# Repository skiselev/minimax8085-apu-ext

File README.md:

# minimax8085-apu-ext
Arithmetic Processor and Extension Board for MiniMax 8085 SBC

## Introduction

The MiniMax 8085 Arithmetic Processor and Extension board adds to [MiniMax 8085 SBC](https://github.com/skiselev/minimax8085) an AMD Am9511A / Intel 8231A Arithmetic Processor Unit (APU), Intel 8255 Programmable Parallel Interface (PPI), Intel 8254 Programmable Interrupt Timer (PIT), and switchable 32 KiB SRAM, that can swapped in instead of MiniMax 8085 on-board ROM. 
It is designed to be plugged on the top of MiniMax8085 using 2x20 pin header / pin socket.

## Hardware Documentation

### Schematic and PCB Layout

[Schematic - Version 1.1](KiCad/Mini8085Ext-Schematic-1.1.pdf)

[PCB Layout - Version 1.1](KiCad/Mini8085Ext-Board-1.1.pdf)

### Design Description

#### Address Decode / Chip Select

The Arithmetic Processor and Extension board uses 74HCT138 3-to-8 decoder U5 for address decode:
* Enable signal E3 of 74HCT138 is connected to IO/M signal, and therefore the decoder is enabled only during I/O operations, when IO/M signal value is HIGH
* Enable signals /E1 and /E2 of 74HCT138 are connected to address lines A6 and A7, so that decoder is enabled when both of these signals are low - 0x00 - 0x3F address range
* Inputs A0-A2 of 74HCT138 are connected to address lines A3 - A4, therefore each output of 74HCT138 is active (LOW) for a block of 8 consequitive I/O addresses, /O0 - for 0x00-0x07, /O1 - for 0x08-0x0F, ... , /O6 for 0x30-0x37, and /O6 for 0x38-0x3F
* Output /O2 of 74HCT138 - /CFG_CS signal - is connected to the input of the 74HCT32 OR gate U8D, another input of that gate is connected to /WD signal. As the result, the output of the gate U8D - CFG_WR is active (LOW) during write cycles to 0x10-0x17 I/O range. CFG_WR is used as a clock signal for 74HCT74 flip-flop U7B, which output /Q is connected to /ROM_DIS signal, that disables MiniMax 8085 on-board ROM, and enables the SRAM on the extension board
* Output /O3 of 74HCT138 - /PPI_CS signal - is connected to the /CS input of 8255 PPI U2, therefore the PPI can be accessed using 0x18 - 0x1F address range
* Output /O4 of 74HCT138 - /PIT_CS signal - is connected to the /CS input of 8254 PIT U3, therefore the PIT can be accessed using 0x20 - 0x27 address range
* Output /O5 of 74HCT138 - /APU_CS signal - is connected to the /CS input of 8231 APU U1, therefore the APU can be accessed using 0x28 - 0x2F address range

#### Arithmetic Processor Unit

Intel 8131A/AMD Am9511A APU is accessed using I/O ports in range 0x28 - 0x2F. The APU uses the lower address bit A0 to select between data register (A0 = 0, I/O address - 0x28) or command/status register (A1 = 1, I/O address - 0x29). The APU is programmed by entering the data into its stack by writing the data register, and then sending the command by writting it to the command register. Once the command completes, the APU will issue an interrupt, which is connected to 8085 TRAP (unmaskable interrupt) signal. The results can be read then from the stack by reading the data register. Please refer to the [Intel 8231A APU Datasheet](Documentation/Intel-8231A_APU-Datasheet.pdf) and the [AMD Am9511A/Am9512 Floating Point Processor Manual](Documentation/AMD-Am9511A-9512-FP_Processor_Manual.pdf) for the detailed programming information.

The APU interface also includes a wait cycle generator built using two 74HCT74 flip flops U6A and U6B, and a few logic gates - U8C, U9A, U9B. This logic generates one or more states when APU is accessed, depending on the /PAUSE output of the APU. The READY signal - pin 1 on header J1 must be connected to the READY signal on MiniMax 8085. Note that READY signal is not provided on the extension connector, therefore a short wire should be used instead.

#### Programmable Parallel Interface

Intel 8255 PPI is accessed using I/O ports in range 0x18 - 0x1F. All the PPI I/O pins are routed to the connector J4. This connector also provides ground and fused 5V power supply. It can be used to connect PPIDE, Extension ROMs, or other peripherals.

Please refer to [Intel 8255 PPI Datasheet](Documentation/Intel-8255_PPI-Datasheet.pdf) for programming information

#### Programmable Interval Timer

Intel 8254 PIT is accessed using I/O ports in range 0x20 - 0x27. The PIT channels are connected as following:
* Channel 0 - used to generate periodic interrupts:
  * The CLK0 input is connected to PIT_CLK - the system clock divided by two using 74HCT74 flip flop U7A. Given the CPU frequency of 3.072 MHz, the PIT_CLK frequency is 1.536 MHz
  * The GATE0 input is tied up, therefore the channel 0 is always enabled
  * The OUT0 output is connected to 8085's RST5_5 interrupt input
  * To generate periodic interrupts, the PIT needs to be configured in mode 2, and RST5.5 interrupt needs to be unmasked.
* Channels 1 and 2 are available for user
  * CLK1 and CLK2 inputs can be either connected to PIT_CLK by placing jumpers across pins 1-2 of JP1 and JP3 respectively, or to an external clock connected to pin 2 (clock) and pin 3 (GND) of JP1 and JP3
  * GATE1 and GATE2 inputs can be: tided up (enabled) by placing jumpers across pins 1-2 of JP2 and JP4 respectively, tided down (disabled) by placing jumpers across pins 2-3 of JP2 and JP4, or connected to an external signal, in such case, the external signal should be connected to pin 2 and the ground to pin 3.
  * OUT1 and OUT2 outputs are available on connectors J2 (OUT1) and J3 (OUT2) respectively

Please refer to [Intel 8254 PIT Datasheet](Documentation/Intel-8254_PIT-Datasheet.pdf) for programming information

#### SRAM Extension

The extension board provides 32 KiB SRAM, which can be switched in at address 0x0000 instead of MiniMax 8085 on-board ROM. The switching is accomplished by writing 0x01 to I/O port 0x10 (CFG register). To switch ROM back, write 0x00 to I/O port 0x10.

### Bill of Materials

#### Version 1.1

[MiniMax8085 Extension on Mouser.com](https://www.mouser.com/ProjectManager/ProjectDetail.aspx?AccessID=52aba2a20b) - View and order all components except of the PCB and the APU.

[MiniMax8085 Extension on OSH Park](https://oshpark.com/shared_projects/crN8OyKx) - View and order the PCB.

Component type     | Reference  | Description                                 | Quantity | Possible sources and notes 
------------------ | ---------- | ------------------------------------------- | -------- | --------------------------
PCB                |            | MiniMax 8085 Extension PCB                  | 1        | Order from a PCB manufacturer of your choice using provided Gerber or KiCad files
Integrated Circut  | U1         | Intel 8231A or AMD Am9511A APU, CERDIP-24   | 1        | eBay
Integrated Circut  | U2         | Intel 8255A, Intersil 82C55A or similar     | 1        | Mouser [968-CP82C55AZ](https://www.mouser.com/ProductDetail/968-CP82C55AZ)
Integrated Circut  | U3         | Intel 8254, Intersil 82C54 or similar       | 1        | Mouser [968-CP82C54Z](https://www.mouser.com/ProductDetail/968-CP82C54Z)
Integrated Circut  | U4         | 62256, AS6C62256-55PCN or similar, DIP-28   | 1        | Mouser [913-AS6C62256-55PCN](https://www.mouser.com/ProductDetail/913-AS6C62256-55PCN)
Integrated Circut  | U5         | 74HCT138 3-to-8 line decoder, DIP-16        | 1        | Mouser [595-SN74AHCT138N](https://www.mouser.com/ProductDetail/595-SN74AHCT138N)<br>Note: Possible replacements: 74HCT138, 74LS138, 74ALS138
Integrated Circut  | U6, U7     | 74HCT74 dual D-type flip flops, DIP-14      | 2        | Mouser [595-SN74AHCT74N](https://www.mouser.com/ProductDetail/595-SN74AHCT74N)<br>Note: Possible replacements: 74HCT74, 74LS74, 74ALS74
Integrated Circut  | U8         | 74HCT32 quad 2-input OR gate, DIP-14        | 1        | Mouser [595-SN74AHCT32N](https://www.mouser.com/ProductDetail/595-SN74AHCT32N)<br>Note: Possible replacements: 74HCT32, 74LS32, 74ALS32
Integrated Circut  | U9         | 74HCT00 quad 2-input NAND gate, DIP-14      | 1        | Mouser [595-SN74AHCT00N](https://www.mouser.com/ProductDetail/595-SN74AHCT00N)<br>Note: Possible replacements: 74HCT00, 74LS00, 74ALS00
DC-DC Converter    | U10        | TBA1-0512E, 5V to 12V, 1W DC-DC Converter, SIP-6 | 1   | Mouser [495-TBA1-0512E](https://www.mouser.com/ProductDetail/495-TBA1-0512E)
IC Socket          | U1, U3     | DIP-24, 600 mil socket                      | 2        | Mouser [649-DILB24P-223TLF](https://www.mouser.com/ProductDetail/649-DILB24P-223TLF)
IC Socket          | U2         | DIP-40, 600 mil socket                      | 1        | Mouser [649-DILB40P223TLF](https://www.mouser.com/ProductDetail/649-DILB40P223TLF)
IC Socket          | U4         | DIP-28, 600 mil socket                      | 1        | Mouser [649-DILB28P223TLF](https://www.mouser.com/ProductDetail/649-DILB28P223TLF)
IC Socket          | U5         | DIP-16, 300 mil socket                      | 1        | Mouser [649-DILB16P-223TLF](https://www.mouser.com/ProductDetail/649-DILB16P-223TLF)
IC Socket          | U6 - U9    | DIP-14, 300 mil socket                      | 4        | Mouser [649-DILB14P-223TLF](https://www.mouser.com/ProductDetail/649-DILB14P-223TLF)
Header             | JP1 - JP4  | 1x3 pin header, 2.54 mm pitch, straight     | 4        | Mouser [649-68000-203HLF](https://www.mouser.com/ProductDetail/649-68000-203HLF)
Jumpers            | JP1 - JP4  | Jumper, 2.54 mm pitch                       | 4        | Mouser [806-SX1100-B](https://www.mouser.com/ProductDetail/806-SX1100-B)
Header             | J1 - J3    | 2x3 pin header, 2.54 mm pitch, right angle  | 1        | Mouser [649-68020-106HLF](https://www.mouser.com/ProductDetail/649-68020-106HLF)
Header             | J4         | 2x13 pin header, 2.54 mm pitch, right angle | 1        | Mouser [649-68021-226HLF](https://www.mouser.com/ProductDetail/649-68021-226HLF)
Header             | J5         | 2x20 pin stacking header, 2.54 mm pitch, straight | 1  | Mouser [855-M20-6102045](https://www.mouser.com/ProductDetail/855-M20-6102045), Mouser [200-ESQ12014LD](https://www.mouser.com/ProductDetail/200-ESQ12014LD)
Capacitor          | C1 - C11   | 0.1 µF, MLCC, 5 mm lead spacing             | 11       | Mouser [810-FG28X7R1H104KNT6](https://www.mouser.com/ProductDetail/810-FG28X7R1H104KNT6)
Capacitor          | C12, C13   | 47 µF, 25V, Electrolytic, 2.5 mm lead spacing | 2      | Mouser [80-A750EK476M1EAAE40](https://www.mouser.com/ProductDetail/80-A750EK476M1EAAE40)
Resistor           | R1 - R3    | 1k                                          | 3        | Mouser [603-MFR-25FBF52-1K](https://www.mouser.com/ProductDetail/603-MFR-25FBF52-1K)
Resistor           | R4, R4     | 4.7k                                        | 2        | Mouser [603-MFR-25FBF52-4K7](https://www.mouser.com/ProductDetail/603-MFR-25FBF52-4K7)
Polyfuse           | F1         | 1.1 A, radial, 5 mm pitch                   | 1        | Mouser [652-MFR110](https://www.mouser.com/ProductDetail/652-MFR110)<br>Note: Optional if not populating J4
Standoff           |            | 15.24 mm x M3, PC/104 stacking standoff     | 4        | Mouser [855-R6104-02](https://www.mouser.com/ProductDetail/855-R6104-02)

## Installing Programming MiniMax 8085 Arithmetic Processor and Extension board

The board stacks together with MiniMax 8085 SBC using PC/104 style 2x20 pin headers. See the BOM above for the recommended part numbers

## Programming MiniMax 8085 Arithmetic Processor and Extension board

### APU

This sample shows how to run the PUPI (PUSH PI) instruction in MON85.

First set interrupt service routine (ISR) for TRAP interrupt. This needs to be done once (possibly repeated if the board is powered down and SRAM content is lost).
The ISR code is:
<pre><code>
        IN      29h     ; READ APU STATUS - CLEAR INTERRUPT
        EI              ; RE-ENABLE INTERRUPTS
        RST     1       ; RETURN CONTROL TO MON85
</code></pre>

MON85 commands:
* C> **E E024** - Edit memory location E024
* E024 00=**DB** - IN 29
* E025 00=**29**
* E026 00=**FB** - EI
* E027 00=**CF** - RST 1
* E028 00=**(Press ESC to exit memory edit mode)**

Next, set MON85 user area to E000. MON85 uses this are for RST interrupts vectors:
* C> **U E000** - Set user area to 0xE000

Send PUPI command to the APU:
* C> **O 29 1A** - Send PUPI command to APU
* BC=4F00  DE=FFD7  HL=001A  SP=FFFE  PC=E027   PSW=0044   FLAGS=-Z---P--

Read back the result from the APU:
* C> **I 28** - Read most significant byte from APU
* DATA=02
* C> **I 28** - Read next byte
* DATA=C9
* C> **I 28** - Read next byte
* DATA=0F
* C> **I 28** - Read the least significant byte from APU
* DATA=DA

### SRAM

The code below copies the MON85 code to the RAM and switches ROM for RAM. Refer to the comments in the code for MON85 instructions. The HEX code is given below after the source code.

Source code:
<pre><code>
; COPY ROM MONITOR TO LOW RAM AND SWITCH ROM FOR LOW RAM
;
; USE THE FOLLOWING MON85 COMMANDS TO RUN:
; C> L E080
; <COPY/UPLOAD HEX>
; C> G E080
; BC=0000  DE=1000  HL=F100  SP=FFA0  PC=E0B2   PSW=FF54   FLAGS=-Z-A-P--
; C>
; 
; COPY ROM MONITOR TO HIGH RAM
        LXI     B,1000H
        LXI     D,0E100H
        LXI     H,0000H

LOOP1:
        MOV     A,M
        XCHG
        MOV     M,A
        XCHG
        INX     D
        INX     H
        DCR     C
        JNZ     0E089H  ; LOOP1
        DCR     B
        JNZ     0E089H  ; LOOP1

; SWAP ROM FOR LOW RAM
        MVI     A,1
        OUT     10H

; COPY MONITOR FROM HIGH RAM TO LOW RAM
        LXI     B,1000H
        LXI     D,0000H
        LXI     H,0E100H

LOOP2:
        MOV     A,M
        XCHG
        MOV     M,A
        XCHG
        INX     D
        INX     H
        DCR     C
        JNZ     0E0A4H  ; LOOP2
        DCR     B
        JNZ     0E0A4H  ; LOOP2

; RETURN TO MONITOR
        RST     1
</code></pre>

HEX code:
<pre><code>
:100000000100101100E12100007EEB77EB13230DBE
:10001000C289E005C289E03E01D310010010110041
:10002000002100E17EEB77EB13230DC2A4E005C2B3
:03003000A4E0CF7A
:00000001FF
</code></pre>

## Release Notes

### Changes

* Version 1.1
  * Fix DC-DC converter footprint
  * Use rounded traces
* Version 1.0
  * Initial design

### Known Issues

* Version 1.1
  * APU interrupt on operation completion should optional. Add a jumper to disconnect /END pin of U1/8231A from /INT signal
* Version 1.0
  * Incorrect footprint for U10 DC-DC converter

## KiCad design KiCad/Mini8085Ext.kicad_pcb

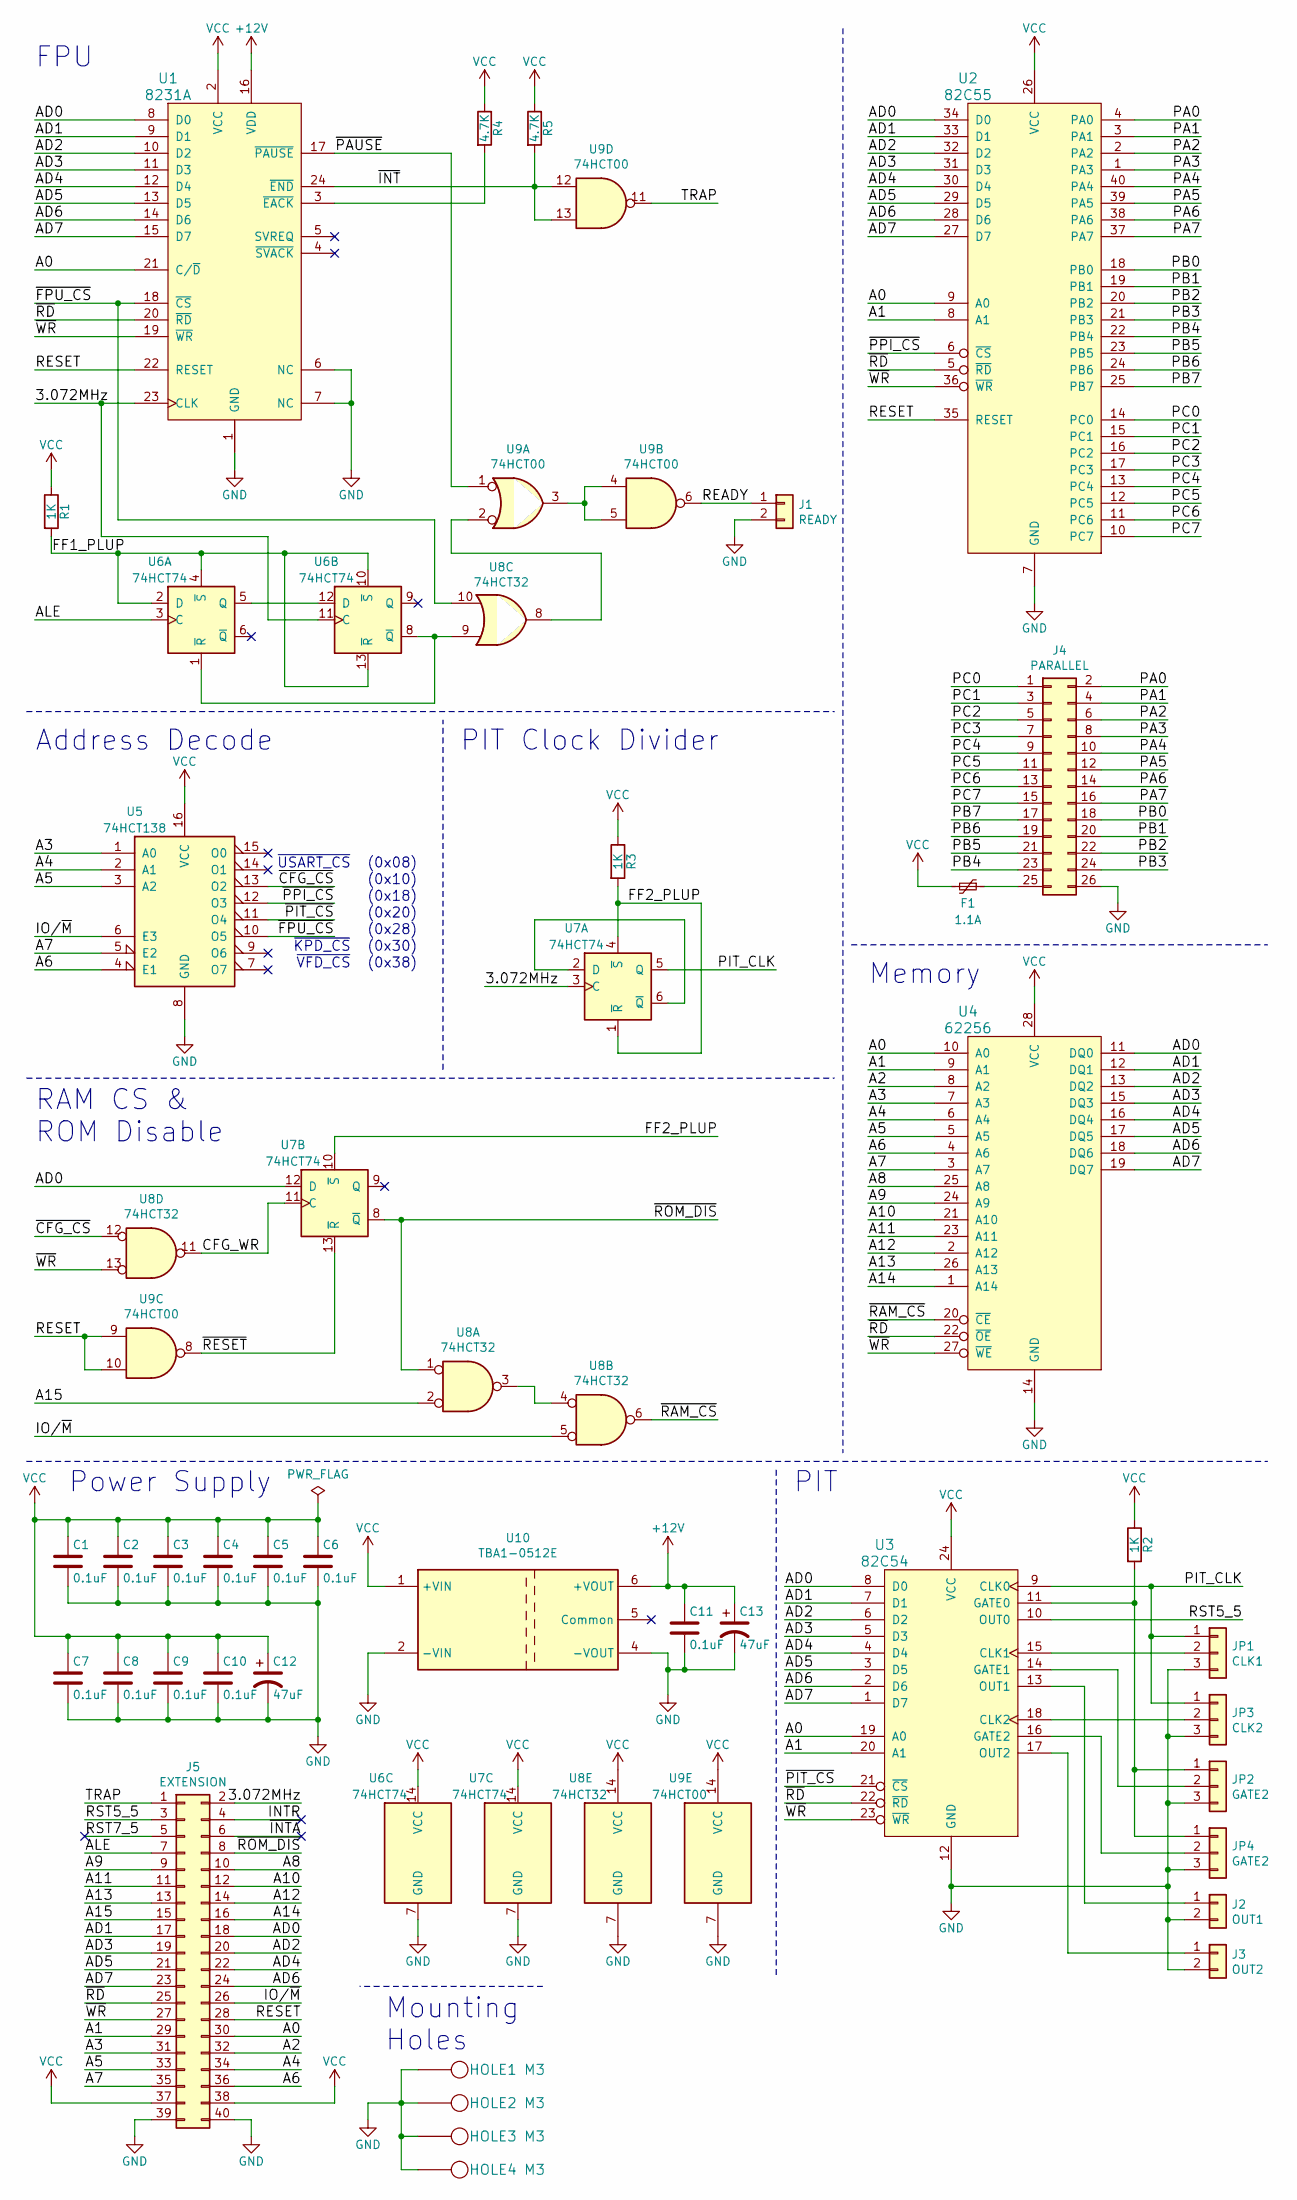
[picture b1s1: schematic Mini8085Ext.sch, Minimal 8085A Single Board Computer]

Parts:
C1, C2, C3, C4, C5, C6, C7, C8, C9, C10, C11: 0.1uF; Cap_Cer_508
C12, C13: 47uF; Cap_Elec_Radial_6.3mm
F1: 1.1A; Cap_Cer_508
HOLE1, HOLE2, HOLE3, HOLE4: M3; MountingHole_3.2mm_M3_Pad_Via
J1: READY; Conn_Pin_Header_2x1_2.54mm
J2: OUT1; Conn_Pin_Header_2x1_2.54mm
J3: OUT2; Conn_Pin_Header_2x1_2.54mm
J4: PARALLEL; Conn_Pin_Header_13x2_2.54mm_Shrouded
J5: EXTENSION; Conn_Pin_Header_20x2_2.54mm
JP1: CLK1; Conn_Pin_Header_3x1_2.54mm
JP2, JP4: GATE2; Conn_Pin_Header_3x1_2.54mm
JP3: CLK2; Conn_Pin_Header_3x1_2.54mm
R1, R2, R3: 1K; Res_762
R4, R5: 4.7K; Res_762
U1: 8231A; IC_DIP24_600
U2: 82C55; IC_DIP40_600
U3: 82C54; IC_DIP24_600
U4: 62256; IC_DIP28_600
U5: 74HCT138; IC_DIP16_300
U6, U7: 74HCT74; IC_DIP14_300
U8: 74HCT32; IC_DIP14_300
U9: 74HCT00; IC_DIP14_300
U10: TBA1-0512E; DC-DC_SIP7

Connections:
+12V: C11.1, C13.1, U1.16 (VDD), U10.6 (+VOUT)
/3.072MHz: J5.2, U1.23 (CLK), U6.11 (C), U7.3 (C)
/A0: J5.30, U1.21 (C/~D), U2.9 (A0), U3.19 (A0), U4.10 (A0)
/A1: J5.29, U2.8 (A1), U3.20 (A1), U4.9 (A1)
/A2: J5.32, U4.8 (A2)
/A3: J5.31, U4.7 (A3), U5.1 (A0)
/A4: J5.34, U4.6 (A4), U5.2 (A1)
/A5: J5.33, U4.5 (A5), U5.3 (A2)
/A6: J5.36, U4.4 (A6), U5.4 (E1)
/A7: J5.35, U4.3 (A7), U5.5 (E2)
/A8: J5.10, U4.25 (A8)
/A9: J5.9, U4.24 (A9)
/A10: J5.12, U4.21 (A10)
/A11: J5.11, U4.23 (A11)
/A12: J5.14, U4.2 (A12)
/A13: J5.13, U4.26 (A13)
/A14: J5.16, U4.1 (A14)
/A15: J5.15, U8.2
/AD0: J5.18, U1.8 (D0), U2.34 (D0), U3.8 (D0), U4.11 (DQ0), U7.12 (D)
/AD1: J5.17, U1.9 (D1), U2.33 (D1), U3.7 (D1), U4.12 (DQ1)
/AD2: J5.20, U1.10 (D2), U2.32 (D2), U3.6 (D2), U4.13 (DQ2)
/AD3: J5.19, U1.11 (D3), U2.31 (D3), U3.5 (D3), U4.15 (DQ3)
/AD4: J5.22, U1.12 (D4), U2.30 (D4), U3.4 (D4), U4.16 (DQ4)
/AD5: J5.21, U1.13 (D5), U2.29 (D5), U3.3 (D5), U4.17 (DQ5)
/AD6: J5.24, U1.14 (D6), U2.28 (D6), U3.2 (D6), U4.18 (DQ6)
/AD7: J5.23, U1.15 (D7), U2.27 (D7), U3.1 (D7), U4.19 (DQ7)
/ALE: J5.7, U6.3 (C)
/CFG_WR: U7.11 (C), U8.11
/FF1_PLUP: R1.2, U6.2 (D), U6.4 (~S), U6.10 (~S), U6.13 (~R)
/FF2_PLUP: R3.2, U7.1 (~R), U7.4 (~S), U7.10 (~S)
/INTR: J5.4
/IO/~M: J5.26, U5.6 (E3), U8.5
/PA0: J4.2, U2.4 (PA0)
/PA1: J4.4, U2.3 (PA1)
/PA2: J4.6, U2.2 (PA2)
/PA3: J4.8, U2.1 (PA3)
/PA4: J4.10, U2.40 (PA4)
/PA5: J4.12, U2.39 (PA5)
/PA6: J4.14, U2.38 (PA6)
/PA7: J4.16, U2.37 (PA7)
/PB0: J4.18, U2.18 (PB0)
/PB1: J4.20, U2.19 (PB1)
/PB2: J4.22, U2.20 (PB2)
/PB3: J4.24, U2.21 (PB3)
/PB4: J4.23, U2.22 (PB4)
/PB5: J4.21, U2.23 (PB5)
/PB6: J4.19, U2.24 (PB6)
/PB7: J4.17, U2.25 (PB7)
/PC0: J4.1, U2.14 (PC0)
/PC1: J4.3, U2.15 (PC1)
/PC2: J4.5, U2.16 (PC2)
/PC3: J4.7, U2.17 (PC3)
/PC4: J4.9, U2.13 (PC4)
/PC5: J4.11, U2.12 (PC5)
/PC6: J4.13, U2.11 (PC6)
/PC7: J4.15, U2.10 (PC7)
/PIT_CLK: JP1.1, JP3.1, U3.9 (CLK0), U7.5 (Q)
/READY: J1.1, U9.6
/RESET: J5.28, U1.22 (RESET), U2.35 (RESET), U9.9, U9.10
/RST5_5: J5.3, U3.10 (OUT0)
/RST7_5: J5.5
/TRAP: J5.1, U9.11
/~CFG_CS: U5.13 (O2), U8.12
/~FPU_CS: U1.18 (~CS), U5.10 (O5), U8.10
/~INT: R5.2, U1.24 (~END), U9.12, U9.13
/~INTA: J5.6
/~PAUSE: U1.17 (~PAUSE), U9.1
/~PIT_CS: U3.21 (~CS), U5.11 (O4)
/~PPI_CS: U2.6 (~CS), U5.12 (O3)
/~RAM_CS: U4.20 (~CE), U8.6
/~RD: J5.25, U1.20 (~RD), U2.5 (~RD), U3.22 (~RD), U4.22 (~OE)
/~RESET: U7.13 (~R), U9.8
/~ROM_DIS: J5.8, U7.8 (~Q), U8.1
/~WR: J5.27, U1.19 (~WR), U2.36 (~WR), U3.23 (~WR), U4.27 (~WE), U8.13
GND: C1.2, C2.2, C3.2, C4.2, C5.2, C6.2, C7.2, C8.2, C9.2, C10.2, C11.2, C12.2, C13.2, HOLE1.1, HOLE2.1, HOLE3.1, HOLE4.1, J1.2, J2.2, J3.2, J4.26, J5.39, J5.40, JP1.3, JP2.3, JP3.3, JP4.3, U1.1 (GND), U1.6 (NC), U1.7 (NC), U2.7 (GND), U3.12 (GND), U4.14 (GND), U5.8 (GND), U6.7 (GND), U7.7 (GND), U8.7 (GND), U9.7 (GND), U10.2 (-VIN), U10.4 (-VOUT)
unnamed: F1.1, J4.25
unnamed: J2.1, U3.13 (OUT1)
unnamed: J3.1, U3.17 (OUT2)
unnamed: JP1.2, U3.15 (CLK1)
unnamed: JP2.1, JP4.1, R2.2, U3.11 (GATE0)
unnamed: JP2.2, U3.14 (GATE1)
unnamed: JP3.2, U3.18 (CLK2)
unnamed: JP4.2, U3.16 (GATE2)
unnamed: R4.2, U1.3 (~EACK)
unnamed: U6.1 (~R), U6.8 (~Q), U8.9
unnamed: U6.5 (Q), U6.12 (D)
unnamed: U7.2 (D), U7.6 (~Q)
unnamed: U8.3, U8.4
unnamed: U8.8, U9.2
unnamed: U9.3, U9.4, U9.5
VCC: C1.1, C2.1, C3.1, C4.1, C5.1, C6.1, C7.1, C8.1, C9.1, C10.1, C12.1, F1.2, J5.37, J5.38, R1.1, R2.1, R3.1, R4.1, R5.1, U1.2 (VCC), U2.26 (VCC), U3.24 (VCC), U4.28 (VCC), U5.16 (VCC), U6.14 (VCC), U7.14 (VCC), U8.14 (VCC), U9.14 (VCC), U10.1 (+VIN)

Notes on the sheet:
Memory
Mounting Holes
RAM CS & ROM Disable
FPU
(0x20)
(0x28)
(0x08)
(0x30)
(0x38)
(0x10)
(0x18)
~USART_CS
~KPD_CS
~VFD_CS
Address Decode
PIT Clock Divider
PIT
Power Supply

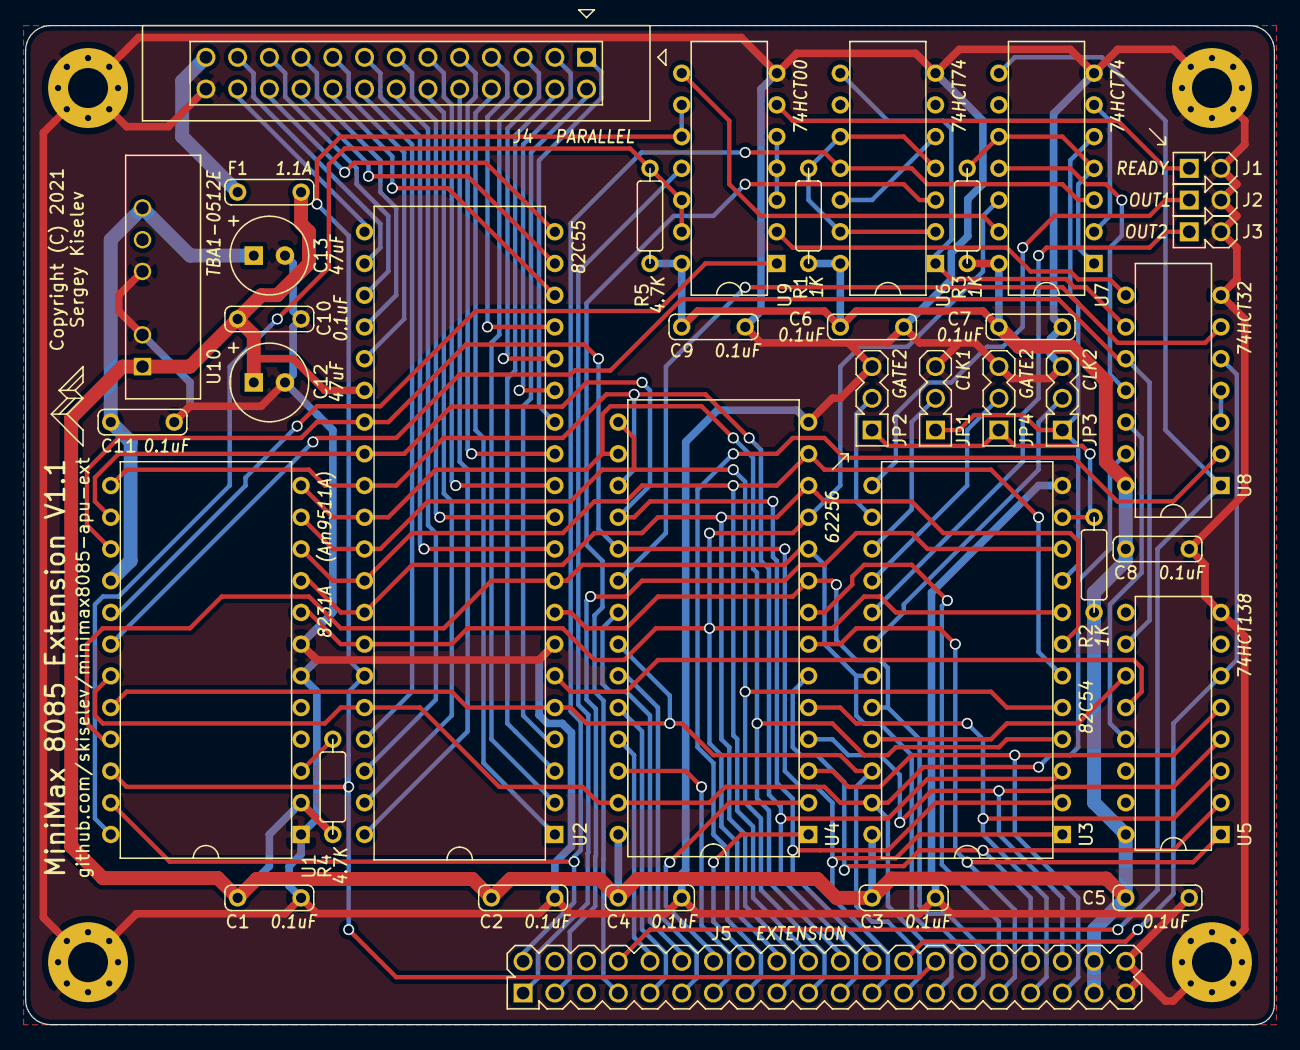
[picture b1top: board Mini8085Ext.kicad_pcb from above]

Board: 2 copper layers, 100.0 x 80.0 mm, 42 parts (0 on the bottom side), 88 nets.

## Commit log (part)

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2022-01-08 README: New file
2022-01-08 README: Add Mouser parts links
2022-01-08 README: Update Mouser project link
2022-01-08 Add KiCad files
2022-01-08 README: Fix schematic link
2022-01-08 Add photo
2022-01-08 Add datasheets and Gerber files

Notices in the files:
KiCad/Mini8085Ext.kicad_pcb:
Copyright (C) 2021
